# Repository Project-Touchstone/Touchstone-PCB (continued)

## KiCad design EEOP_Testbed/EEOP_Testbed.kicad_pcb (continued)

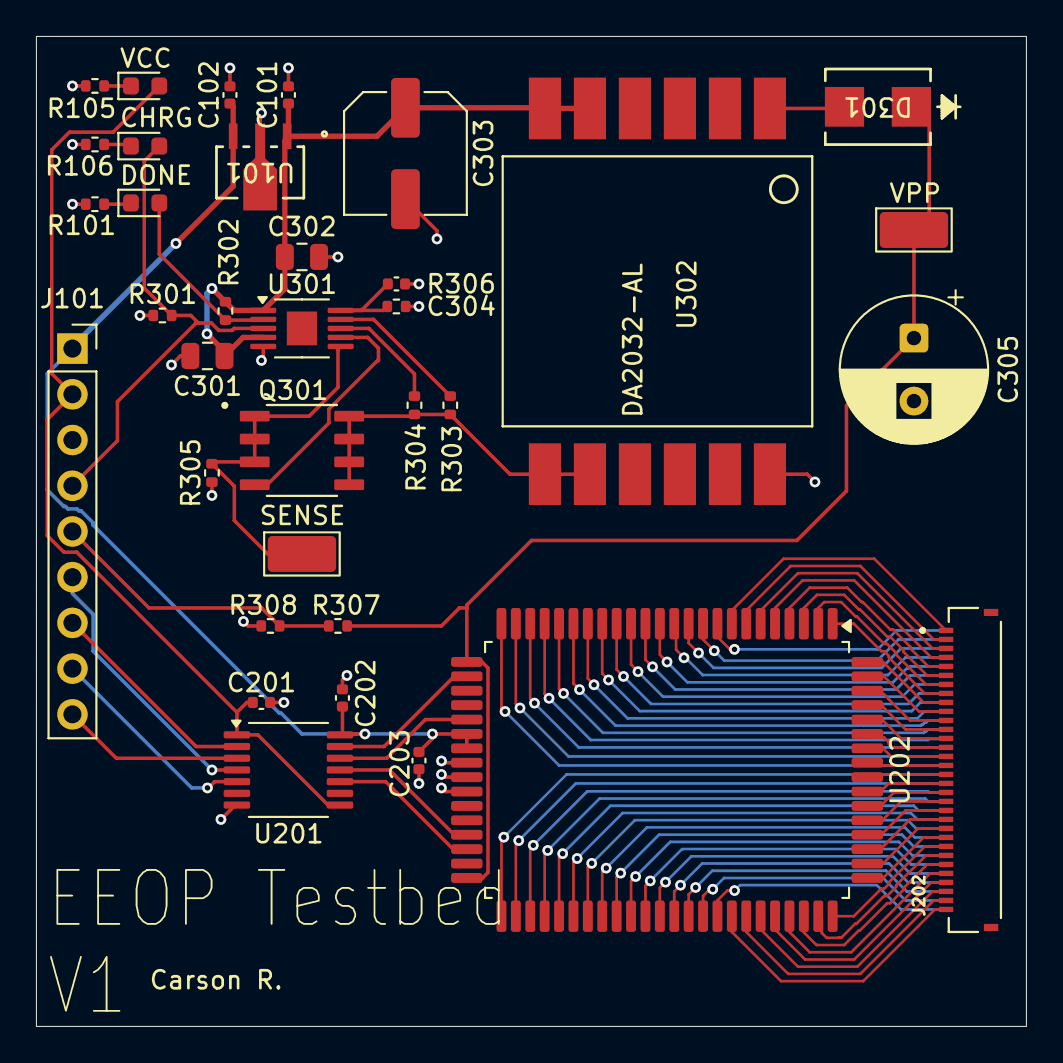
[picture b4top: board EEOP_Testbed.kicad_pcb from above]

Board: 2 copper layers, 55.0 x 55.0 mm, 36 parts (1 on the bottom side), 90 nets.

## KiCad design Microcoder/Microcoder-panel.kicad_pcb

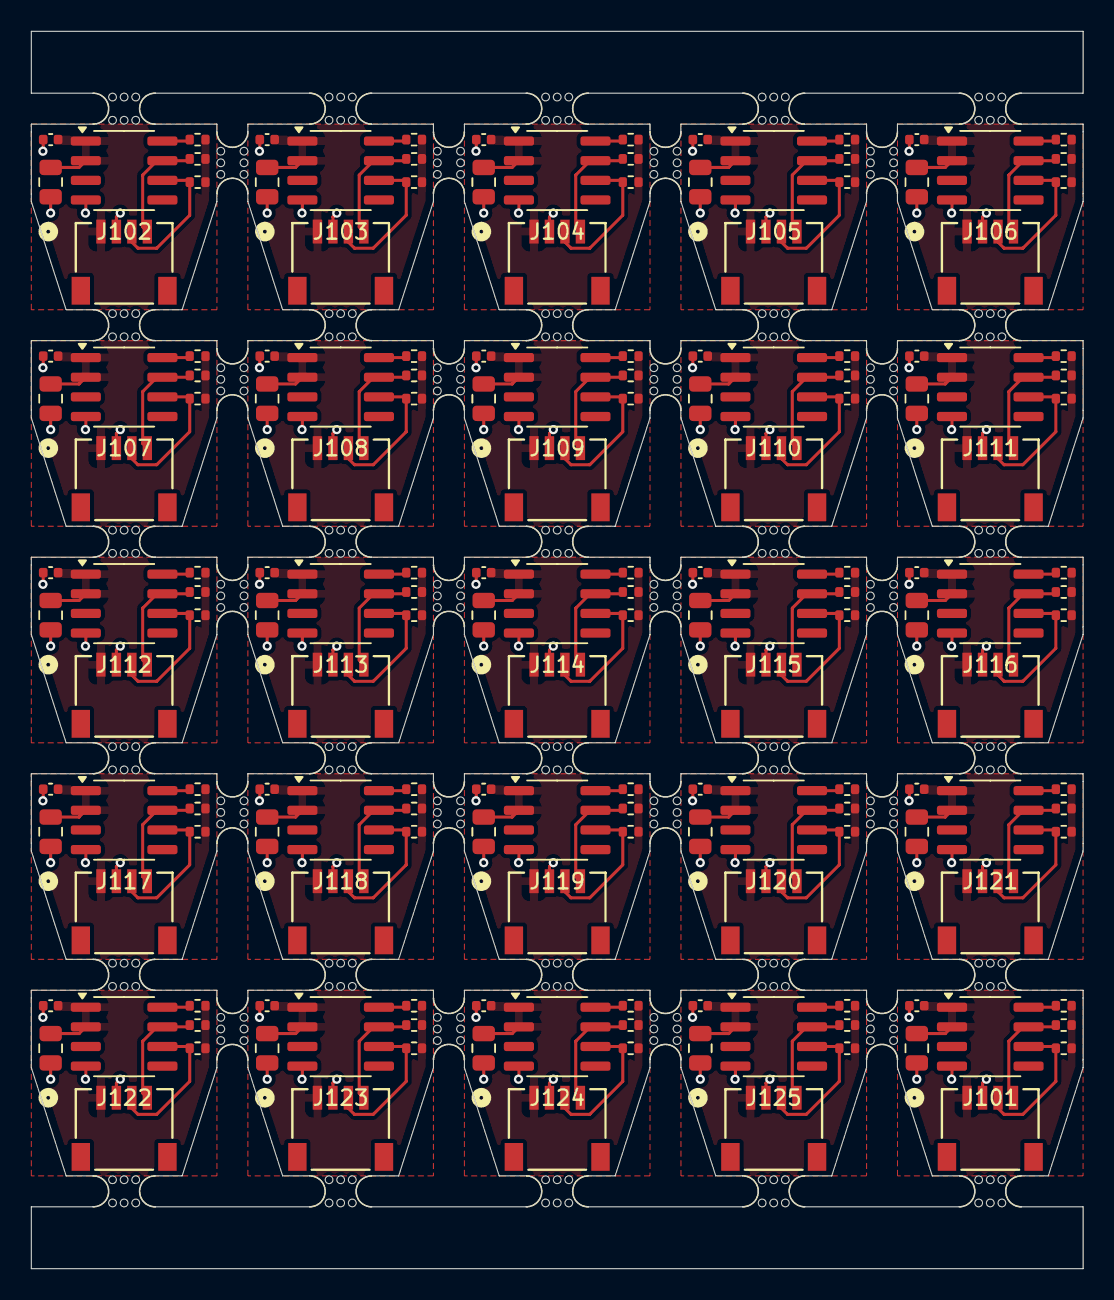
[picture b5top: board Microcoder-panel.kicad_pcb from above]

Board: 2 copper layers, 68.0 x 80.0 mm, 225 parts (0 on the bottom side), 5 nets.

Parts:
C101, C103, C105, C107, C109, C111, C113, C115, C117, C119, C121, C123, C125, C127, C129, C131, C133, C135, C137, C139, C141, C143, C145, C147, C149: 10u; C_0805_2012Metric
C102, C104, C106, C108, C110, C112, C114, C116, C118, C120, C122, C124, C126, C128, C130, C132, C134, C136, C138, C140, C142, C144, C146, C148, C150: 0.1u; C_0402_1005Metric
IC101, IC102, IC103, IC104, IC105, IC106, IC107, IC108, IC109, IC110, IC111, IC112, IC113, IC114, IC115, IC116, IC117, IC118, IC119, IC120, IC121, IC122, IC123, IC124, IC125: AS5600-ASOT; SOIC-8_3.9x4.9mm_P1.27mm
J101, J102, J103, J104, J105, J106, J107, J108, J109, J110, J111, J112, J113, J114, J115, J116, J117, J118, J119, J120, J121, J122, J123, J124, J125: Conn_01x04; CONN_CCSH-W10R-04TR-BK-A_ADA
R101, R102, R103, R104, R105, R106, R107, R108, R109, R110, R111, R112, R113, R114, R115, R116, R117, R118, R119, R120, R121, R122, R123, R124, R125, R126, R127, R128, R129, R130, R131, R132, R133, R134, R135, R136, R137, R138, R139, R140, R141, R142, R143, R144, R145, R146, R147, R148, R149, R150, R151, R152, R153, R154, R155, R156, R157, R158, R159, R160, R161, R162, R163, R164, R165, R166, R167, R168, R169, R170, R171, R172, R173, R174, R175: 10k; R_0402_1005Metric
mouse-bite-2mm-slot, mouse-bite-2mm-slot1, mouse-bite-2mm-slot3, mouse-bite-2mm-slot4, mouse-bite-2mm-slot5, mouse-bite-2mm-slot6, mouse-bite-2mm-slot7, mouse-bite-2mm-slot8, mouse-bite-2mm-slot9, mouse-bite-2mm-slot10, mouse-bite-2mm-slot11, mouse-bite-2mm-slot13, mouse-bite-2mm-slot14, mouse-bite-2mm-slot15, mouse-bite-2mm-slot16, mouse-bite-2mm-slot17, mouse-bite-2mm-slot18, mouse-bite-2mm-slot19, mouse-bite-2mm-slot20, mouse-bite-2mm-slot21, mouse-bite-2mm-slot23, mouse-bite-2mm-slot24, mouse-bite-2mm-slot25, mouse-bite-2mm-slot26, mouse-bite-2mm-slot27, mouse-bite-2mm-slot28, mouse-bite-2mm-slot29, mouse-bite-2mm-slot30, mouse-bite-2mm-slot31, mouse-bite-2mm-slot33, mouse-bite-2mm-slot34, mouse-bite-2mm-slot35, mouse-bite-2mm-slot36, mouse-bite-2mm-slot37, mouse-bite-2mm-slot38, mouse-bite-2mm-slot39, mouse-bite-2mm-slot40, mouse-bite-2mm-slot41, mouse-bite-2mm-slot41#2, mouse-bite-2mm-slot43, mouse-bite-2mm-slot43#2, mouse-bite-2mm-slot44, mouse-bite-2mm-slot45, mouse-bite-2mm-slot45#2, mouse-bite-2mm-slot46, mouse-bite-2mm-slot47, mouse-bite-2mm-slot47#2, mouse-bite-2mm-slot48, mouse-bite-2mm-slot#2, mouse-bite-2mm-slot#3: VAL**; mouse-bite-2mm-slot

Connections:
+3.3V: C101.1, C102.1, C103.1, C104.1, C105.1, C106.1, C107.1, C108.1, C109.1, C110.1, C111.1, C112.1, C113.1, C114.1, C115.1, C116.1, C117.1, C118.1, C119.1, C120.1, C121.1, C122.1, C123.1, C124.1, C125.1, C126.1, C127.1, C128.1, C129.1, C130.1, C131.1, C132.1, C133.1, C134.1, C135.1, C136.1, C137.1, C138.1, C139.1, C140.1, C141.1, C142.1, C143.1, C144.1, C145.1, C146.1, C147.1, C148.1, C149.1, C150.1, IC101.1 (VDD5V), IC101.2 (VDD3V3), IC102.1 (VDD5V), IC102.2 (VDD3V3), IC103.1 (VDD5V), IC103.2 (VDD3V3), IC104.1 (VDD5V), IC104.2 (VDD3V3), IC105.1 (VDD5V), IC105.2 (VDD3V3), IC106.1 (VDD5V), IC106.2 (VDD3V3), IC107.1 (VDD5V), IC107.2 (VDD3V3), IC108.1 (VDD5V), IC108.2 (VDD3V3), IC109.1 (VDD5V), IC109.2 (VDD3V3), IC110.1 (VDD5V), IC110.2 (VDD3V3), IC111.1 (VDD5V), IC111.2 (VDD3V3), IC112.1 (VDD5V), IC112.2 (VDD3V3), IC113.1 (VDD5V), IC113.2 (VDD3V3), IC114.1 (VDD5V), IC114.2 (VDD3V3), IC115.1 (VDD5V), IC115.2 (VDD3V3), IC116.1 (VDD5V), IC116.2 (VDD3V3), IC117.1 (VDD5V), IC117.2 (VDD3V3), IC118.1 (VDD5V), IC118.2 (VDD3V3), IC119.1 (VDD5V), IC119.2 (VDD3V3), IC120.1 (VDD5V), IC120.2 (VDD3V3), IC121.1 (VDD5V), IC121.2 (VDD3V3), IC122.1 (VDD5V), IC122.2 (VDD3V3), IC123.1 (VDD5V), IC123.2 (VDD3V3), IC124.1 (VDD5V), IC124.2 (VDD3V3), IC125.1 (VDD5V), IC125.2 (VDD3V3), J101.1, J102.1, J103.1, J104.1, J105.1, J106.1, J107.1, J108.1, J109.1, J110.1, J111.1, J112.1, J113.1, J114.1, J115.1, J116.1, J117.1, J118.1, J119.1, J120.1, J121.1, J122.1, J123.1, J124.1, J125.1, R101.1, R102.1, R103.1, R104.1, R105.1, R106.1, R107.1, R108.1, R109.1, R110.1, R111.1, R112.1, R113.1, R114.1, R115.1, R116.1, R117.1, R118.1, R119.1, R120.1, R121.1, R122.1, R123.1, R124.1, R125.1, R126.1, R127.1, R128.1, R129.1, R130.1, R131.1, R132.1, R133.1, R134.1, R135.1, R136.1, R137.1, R138.1, R139.1, R140.1, R141.1, R142.1, R143.1, R144.1, R145.1, R146.1, R147.1, R148.1, R149.1, R150.1, R151.1, R152.1, R153.1, R154.1, R155.1, R156.1, R157.1, R158.1, R159.1, R160.1, R161.1, R162.1, R163.1, R164.1, R165.1, R166.1, R167.1, R168.1, R169.1, R170.1, R171.1, R172.1, R173.1, R174.1, R175.1
/SCL: IC101.7 (SCL), IC102.7 (SCL), IC103.7 (SCL), IC104.7 (SCL), IC105.7 (SCL), IC106.7 (SCL), IC107.7 (SCL), IC108.7 (SCL), IC109.7 (SCL), IC110.7 (SCL), IC111.7 (SCL), IC112.7 (SCL), IC113.7 (SCL), IC114.7 (SCL), IC115.7 (SCL), IC116.7 (SCL), IC117.7 (SCL), IC118.7 (SCL), IC119.7 (SCL), IC120.7 (SCL), IC121.7 (SCL), IC122.7 (SCL), IC123.7 (SCL), IC124.7 (SCL), IC125.7 (SCL), J101.4, J102.4, J103.4, J104.4, J105.4, J106.4, J107.4, J108.4, J109.4, J110.4, J111.4, J112.4, J113.4, J114.4, J115.4, J116.4, J117.4, J118.4, J119.4, J120.4, J121.4, J122.4, J123.4, J124.4, J125.4, R102.2, R105.2, R108.2, R111.2, R114.2, R117.2, R120.2, R123.2, R126.2, R129.2, R132.2, R135.2, R138.2, R141.2, R144.2, R147.2, R150.2, R153.2, R156.2, R159.2, R162.2, R165.2, R168.2, R171.2, R174.2
/SDA: IC101.6 (SDA), IC102.6 (SDA), IC103.6 (SDA), IC104.6 (SDA), IC105.6 (SDA), IC106.6 (SDA), IC107.6 (SDA), IC108.6 (SDA), IC109.6 (SDA), IC110.6 (SDA), IC111.6 (SDA), IC112.6 (SDA), IC113.6 (SDA), IC114.6 (SDA), IC115.6 (SDA), IC116.6 (SDA), IC117.6 (SDA), IC118.6 (SDA), IC119.6 (SDA), IC120.6 (SDA), IC121.6 (SDA), IC122.6 (SDA), IC123.6 (SDA), IC124.6 (SDA), IC125.6 (SDA), J101.3, J102.3, J103.3, J104.3, J105.3, J106.3, J107.3, J108.3, J109.3, J110.3, J111.3, J112.3, J113.3, J114.3, J115.3, J116.3, J117.3, J118.3, J119.3, J120.3, J121.3, J122.3, J123.3, J124.3, J125.3, R101.2, R104.2, R107.2, R110.2, R113.2, R116.2, R119.2, R122.2, R125.2, R128.2, R131.2, R134.2, R137.2, R140.2, R143.2, R146.2, R149.2, R152.2, R155.2, R158.2, R161.2, R164.2, R167.2, R170.2, R173.2
GND: C101.2, C102.2, C103.2, C104.2, C105.2, C106.2, C107.2, C108.2, C109.2, C110.2, C111.2, C112.2, C113.2, C114.2, C115.2, C116.2, C117.2, C118.2, C119.2, C120.2, C121.2, C122.2, C123.2, C124.2, C125.2, C126.2, C127.2, C128.2, C129.2, C130.2, C131.2, C132.2, C133.2, C134.2, C135.2, C136.2, C137.2, C138.2, C139.2, C140.2, C141.2, C142.2, C143.2, C144.2, C145.2, C146.2, C147.2, C148.2, C149.2, C150.2, IC101.4 (GND), IC102.4 (GND), IC103.4 (GND), IC104.4 (GND), IC105.4 (GND), IC106.4 (GND), IC107.4 (GND), IC108.4 (GND), IC109.4 (GND), IC110.4 (GND), IC111.4 (GND), IC112.4 (GND), IC113.4 (GND), IC114.4 (GND), IC115.4 (GND), IC116.4 (GND), IC117.4 (GND), IC118.4 (GND), IC119.4 (GND), IC120.4 (GND), IC121.4 (GND), IC122.4 (GND), IC123.4 (GND), IC124.4 (GND), IC125.4 (GND), J101.2, J102.2, J103.2, J104.2, J105.2, J106.2, J107.2, J108.2, J109.2, J110.2, J111.2, J112.2, J113.2, J114.2, J115.2, J116.2, J117.2, J118.2, J119.2, J120.2, J121.2, J122.2, J123.2, J124.2, J125.2
unnamed: IC101.8 (DIR), IC102.8 (DIR), IC103.8 (DIR), IC104.8 (DIR), IC105.8 (DIR), IC106.8 (DIR), IC107.8 (DIR), IC108.8 (DIR), IC109.8 (DIR), IC110.8 (DIR), IC111.8 (DIR), IC112.8 (DIR), IC113.8 (DIR), IC114.8 (DIR), IC115.8 (DIR), IC116.8 (DIR), IC117.8 (DIR), IC118.8 (DIR), IC119.8 (DIR), IC120.8 (DIR), IC121.8 (DIR), IC122.8 (DIR), IC123.8 (DIR), IC124.8 (DIR), IC125.8 (DIR), R103.2, R106.2, R109.2, R112.2, R115.2, R118.2, R121.2, R124.2, R127.2, R130.2, R133.2, R136.2, R139.2, R142.2, R145.2, R148.2, R151.2, R154.2, R157.2, R160.2, R163.2, R166.2, R169.2, R172.2, R175.2

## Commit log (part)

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2025-12-23 Random changes
2026-05-23 Fixed soldermask expansion
2026-06-10 Cleaned up folder, made dedicated encoder board
2026-06-13 Finished routing for Hydra V2
2026-06-13 Used correct flip flop for CS sequencing, added pullup
